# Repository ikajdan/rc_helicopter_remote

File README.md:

# RC Helicopter Remote

## Overview

This project is a custom PCB-based remote controller for an RC helicopter, built around the STM32L452RET6 microcontroller. It interfaces with two joysticks, four buttons, and two potentiometers to capture user input and transmits control data wirelessly via the NRF24L01 module to the helicopter's mainboard.

It complements the [Mainboard PCB](https://github.com/ikajdan/rc_helicopter_mainboard) and is developed in parallel with it as part of the same system.

## Features

The board features an STM32L452RET6 microcontroller, powered by a Li-Ion battery regulated to 3.3 V. It includes a 16 MHz crystal oscillator for accurate timing and clocking. Input devices such as two joysticks (X, Y, S), multiple buttons (SW1–SW4), and two analog potentiometers are connected directly to GPIO pins. Wireless communication is handled by the NRF24L01 module via SPI. Several status LEDs provide user feedback.

## PCB Design

This is a 2-layer compact PCB designed for handheld use, with easy access to controls and routing for digital and analog signals.

| Front View                            | Back View                           |
|---------------------------------------|-------------------------------------|
|  |  |

## Power Supply

The power supply uses an LTC3440 buck-boost converter to step the battery voltage down to 3.3 V. Key components include a 10 µH inductor, 22 µF output capacitor, and feedback resistors (R3 = 340 kΩ, R5 = 200 kΩ, R4 = 15 kΩ) to set the output voltage. The converter is configured for efficient operation across a wide input range and includes filtering components for stability. A power switch and 10 µF input capacitor (C10) are included for basic input protection and noise reduction.

## License

This project is licensed under the [CERN Open Hardware Licence Version 2 - Permissive (CERN-OHL-P)](https://ohwr.org/cern_ohl_p_v2.txt).
You are free to use, modify, and distribute this design, provided you retain notices and disclaimers as specified in the license terms. See the [LICENSE](LICENSE.md) file for full details.

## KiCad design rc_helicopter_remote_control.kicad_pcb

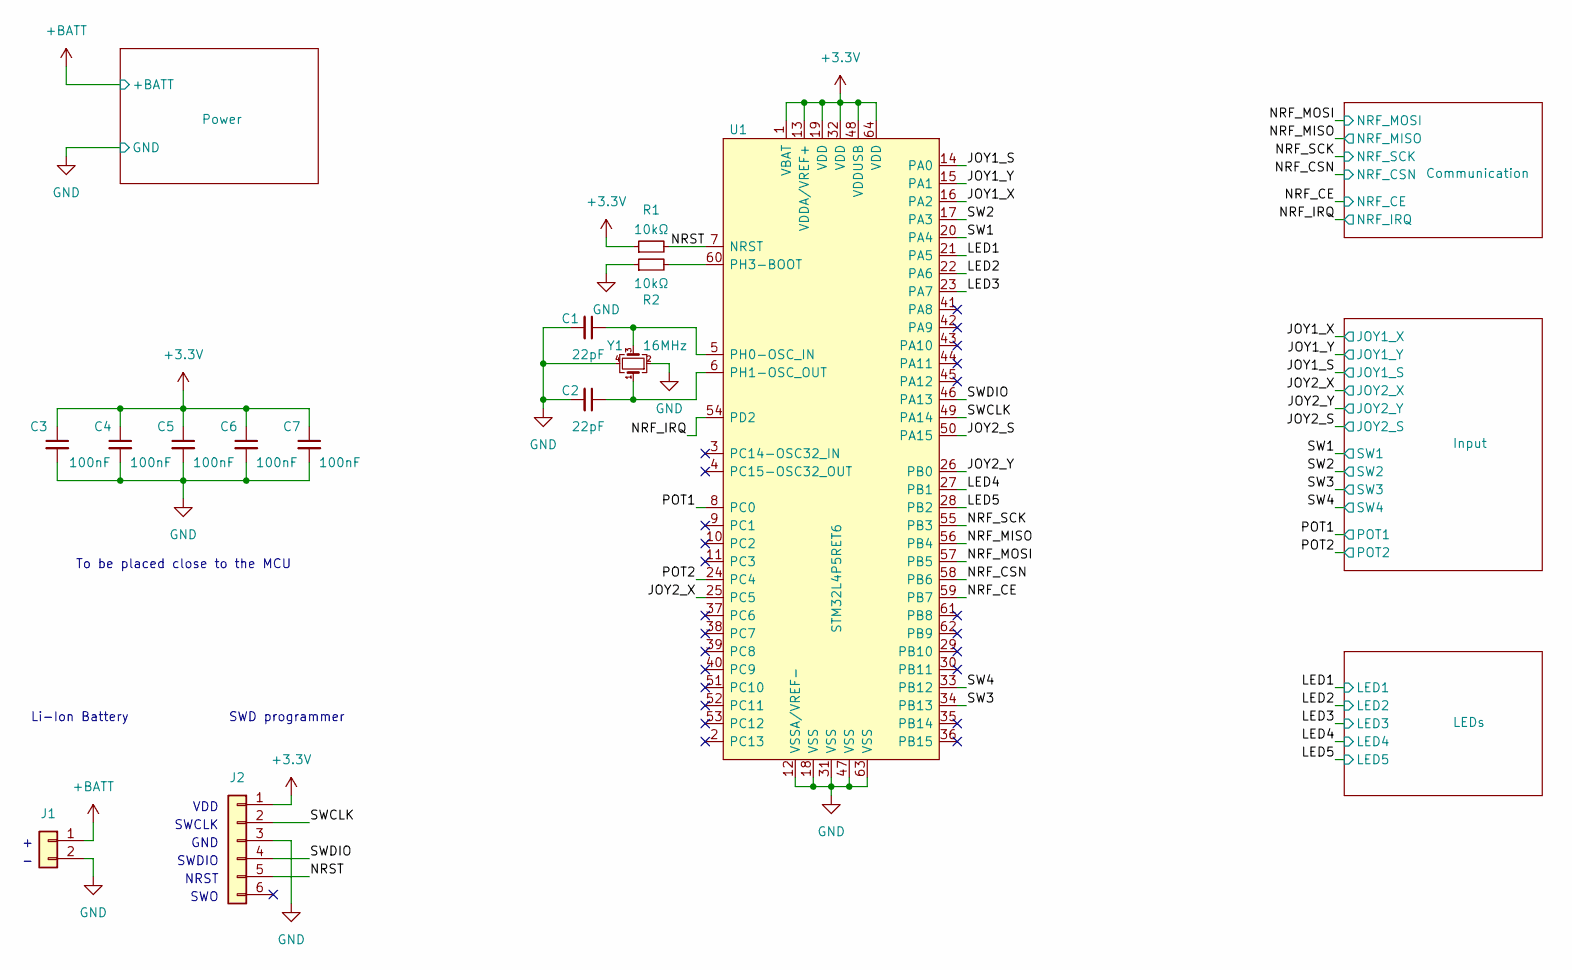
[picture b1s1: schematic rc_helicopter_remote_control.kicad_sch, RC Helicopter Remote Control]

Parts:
C1, C2: 22pF; C_0603_1608Metric
C3, C4, C5, C6, C7: 100nF; C_0603_1608Metric
J1: Battery Pack; Molex_KK-254_AE-6410-02A_1x02_P2.54mm_Vertical
J2: SWD; PinHeader_1x06_P2.54mm_Vertical_SMD_Pin1Left
R1, R2: 10kΩ; R_0603_1608Metric
U1: STM32L4P5RET6; LQFP-64_10x10mm_P0.5mm
Y1: 16MHz; Crystal_SMD_3225-4Pin_3.2x2.5mm

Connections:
+3.3V: C3.1, C4.1, C5.1, C6.1, C7.1, J2.1, R1.1, U1.1 (VBAT), U1.13 (VDDA/VREF+), U1.19 (VDD), U1.32 (VDD), U1.48 (VDDUSB), U1.64 (VDD); also elsewhere on the board
+BATT: J1.1; also elsewhere on the board
/JOY1_S: U1.14 (PA0); also elsewhere on the board
/JOY1_X: U1.16 (PA2); also elsewhere on the board
/JOY1_Y: U1.15 (PA1); also elsewhere on the board
/JOY2_S: U1.50 (PA15); also elsewhere on the board
/JOY2_X: U1.25 (PC5); also elsewhere on the board
/JOY2_Y: U1.26 (PB0); also elsewhere on the board
/LED1: U1.21 (PA5); also elsewhere on the board
/LED2: U1.22 (PA6); also elsewhere on the board
/LED3: U1.23 (PA7); also elsewhere on the board
/LED4: U1.27 (PB1); also elsewhere on the board
/LED5: U1.28 (PB2); also elsewhere on the board
/NRF_CE: U1.59 (PB7); also elsewhere on the board
/NRF_CSN: U1.58 (PB6); also elsewhere on the board
/NRF_IRQ: U1.54 (PD2); also elsewhere on the board
/NRF_MISO: U1.56 (PB4); also elsewhere on the board
/NRF_MOSI: U1.57 (PB5); also elsewhere on the board
/NRF_SCK: U1.55 (PB3); also elsewhere on the board
/NRST: J2.5, R1.2, U1.7 (NRST)
/POT1: U1.8 (PC0); also elsewhere on the board
/POT2: U1.24 (PC4); also elsewhere on the board
/SW1: U1.20 (PA4); also elsewhere on the board
/SW2: U1.17 (PA3); also elsewhere on the board
/SW3: U1.34 (PB13); also elsewhere on the board
/SW4: U1.33 (PB12); also elsewhere on the board
/SWCLK: J2.2, U1.49 (PA14)
/SWDIO: J2.4, U1.46 (PA13)
GND: C1.2, C2.2, C3.2, C4.2, C5.2, C6.2, C7.2, J1.2, J2.3, R2.1, U1.12 (VSSA/VREF-), U1.18 (VSS), U1.31 (VSS), U1.47 (VSS), U1.63 (VSS), Y1.2, Y1.4; also elsewhere on the board
unnamed: C1.1, U1.5 (PH0-OSC_IN), Y1.3
unnamed: C2.1, U1.6 (PH1-OSC_OUT), Y1.1
unnamed: R2.2, U1.60 (PH3-BOOT)

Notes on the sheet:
Li-Ion Battery
SWDIO
To be placed close to the MCU
NRST
VDD
SWD programmer
GND
SWCLK
SWO

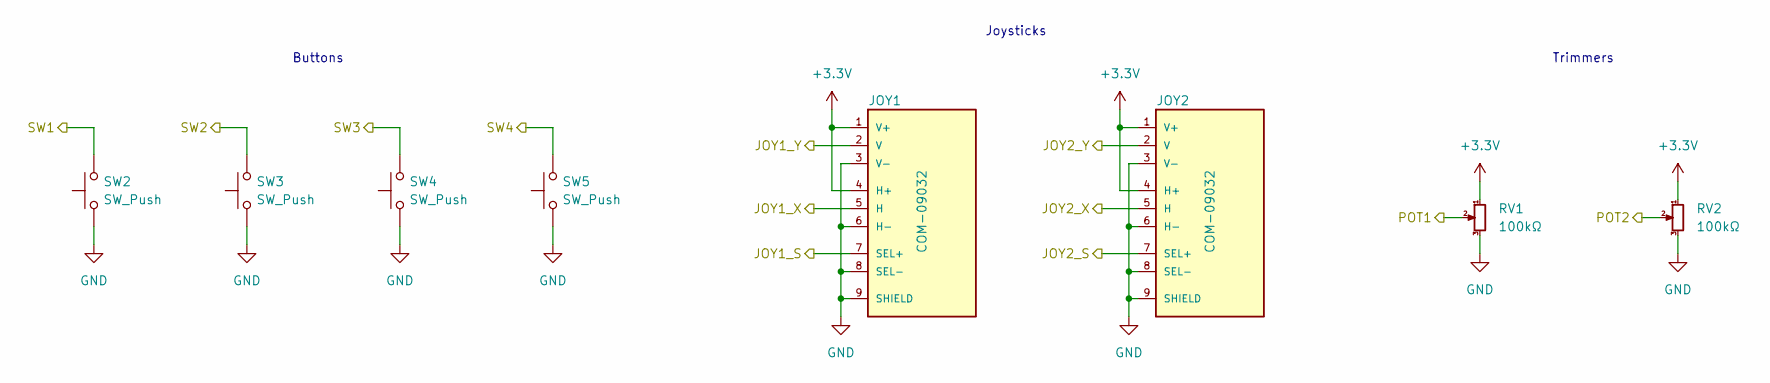
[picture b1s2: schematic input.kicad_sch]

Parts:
JOY1, JOY2: COM-09032; XDCR_COM-09032; PARTREV N/A
RV1, RV2: 100kΩ; Potentiometer_ACP_CA14V-15_Vertical
SW2, SW3, SW4, SW5: SW_Push; SW_PUSH_6mm_H13mm

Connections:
+3.3V: JOY1.1 (V+), JOY1.4 (H+), JOY2.1 (V+), JOY2.4 (H+), RV1.1, RV2.1; also elsewhere on the board
/JOY1_S: JOY1.7 (SEL+); also elsewhere on the board
/JOY1_X: JOY1.5 (H); also elsewhere on the board
/JOY1_Y: JOY1.2 (V); also elsewhere on the board
/JOY2_S: JOY2.7 (SEL+); also elsewhere on the board
/JOY2_X: JOY2.5 (H); also elsewhere on the board
/JOY2_Y: JOY2.2 (V); also elsewhere on the board
/POT1: RV1.2; also elsewhere on the board
/POT2: RV2.2; also elsewhere on the board
/SW1: SW2.1; also elsewhere on the board
/SW2: SW3.1; also elsewhere on the board
/SW3: SW4.1; also elsewhere on the board
/SW4: SW5.1; also elsewhere on the board
GND: JOY1.3 (V-), JOY1.6 (H-), JOY1.8 (SEL-), JOY1.9 (SHIELD), JOY2.3 (V-), JOY2.6 (H-), JOY2.8 (SEL-), JOY2.9 (SHIELD), RV1.3, RV2.3, SW2.2, SW3.2, SW4.2, SW5.2; also elsewhere on the board

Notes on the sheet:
Trimmers
Joysticks
Buttons

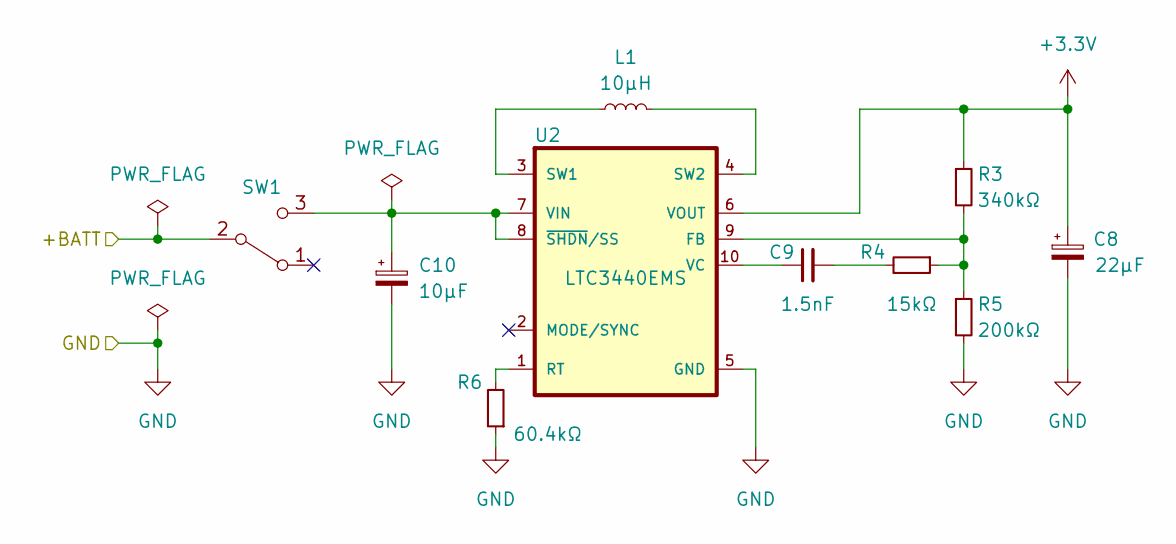
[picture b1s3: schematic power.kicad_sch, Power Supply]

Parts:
C8: 22μF; CP_Elec_6.3x5.4
C9: 1.5nF; C_0603_1608Metric
C10: 10μF; CP_Elec_6.3x5.4
L1: 10μH; L_Bourns-SRN4018
R3: 340kΩ; R_0603_1608Metric
R4: 15kΩ; R_0603_1608Metric
R5: 200kΩ; R_0603_1608Metric
R6: 60.4kΩ; R_0603_1608Metric
SW1: SW_SPST; SW_Slide_1P2T_CK_OS102011MS2Q
U2: LTC3440EMS; MSOP-10_3x3mm_P0.5mm; MPN LTC3440EMS#PBF

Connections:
+3.3V: C8.1, R3.1, U2.6 (VOUT); also elsewhere on the board
+BATT: SW1.2 (B); also elsewhere on the board
GND: C8.2, C10.2, R5.2, R6.1, U2.5 (GND); also elsewhere on the board
unnamed: C9.1, U2.10 (VC)
unnamed: C9.2, R4.2
unnamed: C10.1, SW1.3 (C), U2.7 (VIN), U2.8 (~SHDN/SS)
unnamed: L1.1, U2.3 (SW1)
unnamed: L1.2, U2.4 (SW2)
unnamed: R3.2, R4.1, R5.1, U2.9 (FB)
unnamed: R6.2, U2.1 (RT)

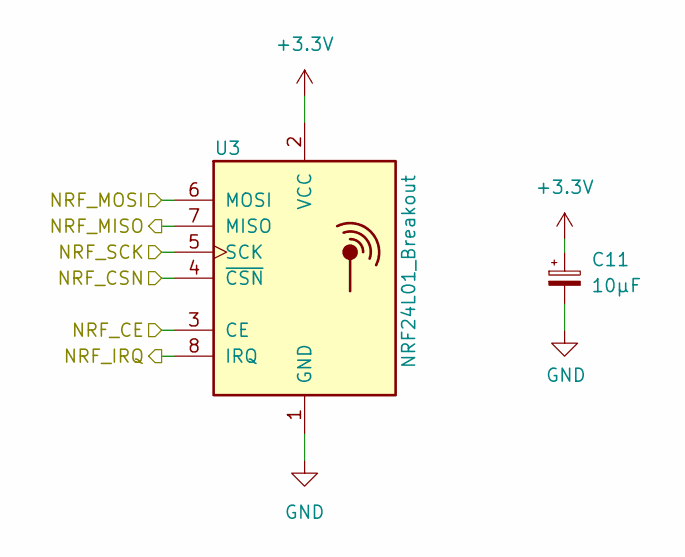
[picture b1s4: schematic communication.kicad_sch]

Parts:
C11: 10μF; CP_EIA-3216-10_Kemet-I
U3: NRF24L01_Breakout; nRF24L01_Breakout

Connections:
+3.3V: C11.1, U3.2 (VCC); also elsewhere on the board
/NRF_CE: U3.3 (CE); also elsewhere on the board
/NRF_CSN: U3.4 (~CSN); also elsewhere on the board
/NRF_IRQ: U3.8 (IRQ); also elsewhere on the board
/NRF_MISO: U3.7 (MISO); also elsewhere on the board
/NRF_MOSI: U3.6 (MOSI); also elsewhere on the board
/NRF_SCK: U3.5 (SCK); also elsewhere on the board
GND: C11.2, U3.1 (GND); also elsewhere on the board

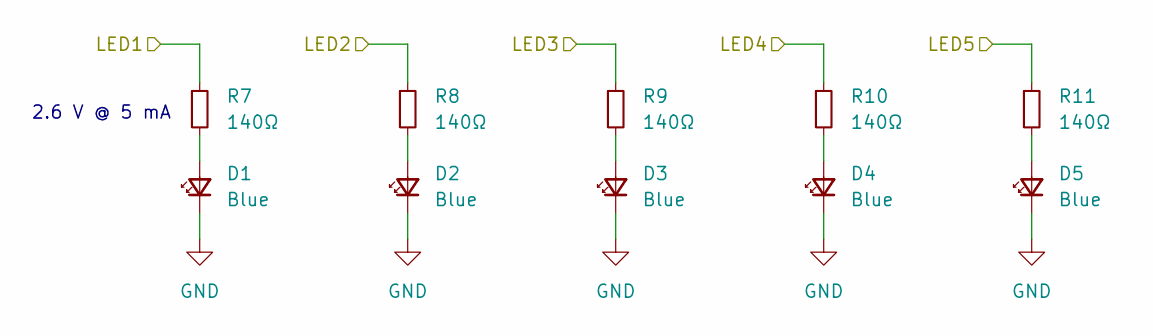
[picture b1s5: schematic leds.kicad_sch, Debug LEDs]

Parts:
D1, D2, D3, D4, D5: Blue; LED_0603_1608Metric
R7, R8, R9, R10, R11: 140Ω; R_0603_1608Metric

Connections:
/LED1: R7.1; also elsewhere on the board
/LED2: R8.1; also elsewhere on the board
/LED3: R9.1; also elsewhere on the board
/LED4: R10.1; also elsewhere on the board
/LED5: R11.1; also elsewhere on the board
GND: D1.1 (K), D2.1 (K), D3.1 (K), D4.1 (K), D5.1 (K); also elsewhere on the board
unnamed: D1.2 (A), R7.2
unnamed: D2.2 (A), R8.2
unnamed: D3.2 (A), R9.2
unnamed: D4.2 (A), R10.2
unnamed: D5.2 (A), R11.2

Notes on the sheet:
2.6 V @ 5 mA

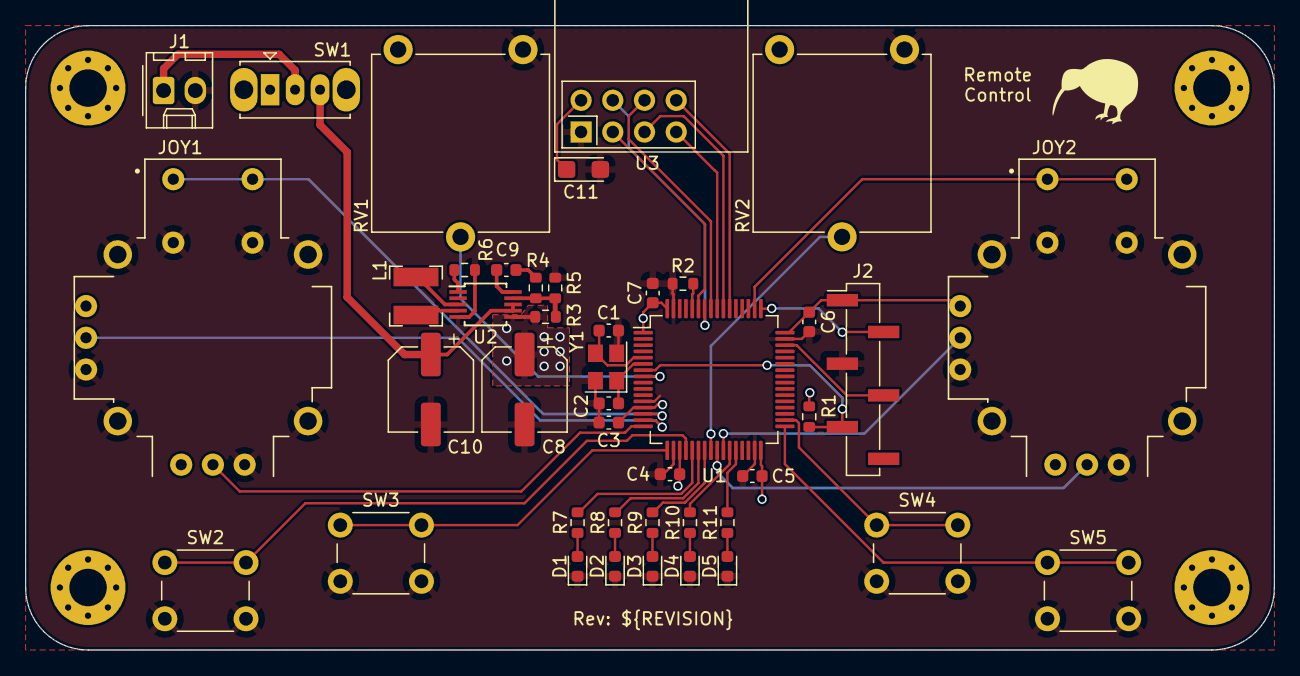
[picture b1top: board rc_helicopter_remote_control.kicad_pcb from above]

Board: 2 copper layers, 100.0 x 50.0 mm, 43 parts (0 on the bottom side), 44 nets.

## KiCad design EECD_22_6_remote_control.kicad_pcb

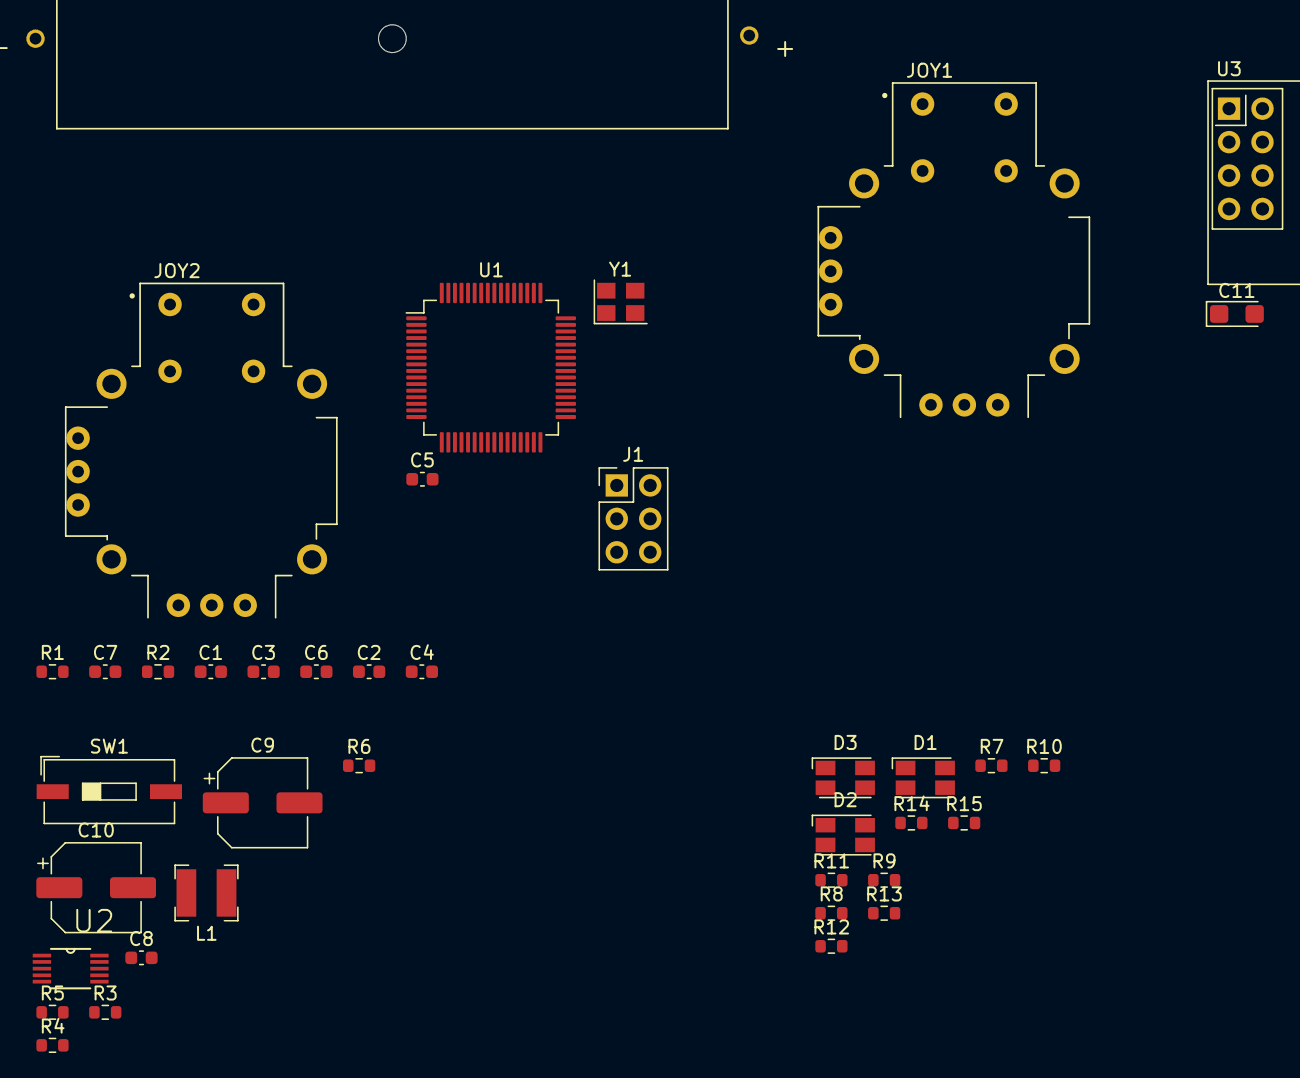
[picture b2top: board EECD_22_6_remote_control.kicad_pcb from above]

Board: 2 copper layers, 39 parts (0 on the bottom side), 47 nets, no tracks yet.

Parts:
BT1: Li-Ion; BAT_BCAAAW
C1, C2: 22pF; C_0603_1608Metric
C3, C4, C5, C6, C7: 100nF; C_0603_1608Metric
C8: 1.5nF; C_0603_1608Metric
C9: 22μF; CP_Elec_6.3x5.4
C10: 10μF; CP_Elec_6.3x5.4
C11: 10μF; CP_EIA-3216-10_Kemet-I
D1, D2, D3: LED_RGBK; LED_Avago_PLCC4_3.2x2.8mm_CW
J1: SWD; PinHeader_2x03_P2.54mm_Vertical
JOY1, JOY2: COM-09032; XDCR_COM-09032
L1: 10μH; L_Bourns-SRN4018
R1, R2: 10kΩ; R_0603_1608Metric
R3: 340kΩ; R_0603_1608Metric
R4: 15kΩ; R_0603_1608Metric
R5: 60.4kΩ; R_0603_1608Metric
R6: 200kΩ; R_0603_1608Metric
R7, R8, R9: 180Ω; R_0603_1608Metric
R10, R11, R12, R13, R14, R15: 100Ω; R_0603_1608Metric
SW1: SW_SPST; SW_DIP_SPSTx01_Slide_9.78x4.72mm_W8.61mm_P2.54mm
U1: STM32L4P5RET6; LQFP-64_10x10mm_P0.5mm
U2: LTC3440EMS; SOP50P490X110-10N
U3: NRF24L01_Breakout; nRF24L01_Breakout
Y1: 16MHz; Crystal_SMD_3225-4Pin_3.2x2.5mm

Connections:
+3.3V: C3.1, C4.1, C5.1, C6.1, C7.1, C9.2, C11.1, D1.4 (K), D2.4 (K), D3.4 (K), J1.1, JOY1.H1 (H+), JOY1.V1 (V+), JOY2.H1 (H+), JOY2.V1 (V+), R1.1, R3.1, U1.1 (VBAT), U1.13 (VDDA/VREF+), U1.19 (VDD), U1.32 (VDD), U1.48 (VDDUSB), U1.64 (VDD), U2.6 (VOUT), U3.2 (VCC)
+BATT: BT1.1 (+), SW1.1 (A)
/JOY1_S: JOY1.B1A (SEL+), U1.16 (PA2)
/JOY1_X: JOY1.H2 (H), U1.15 (PA1)
/JOY1_Y: JOY1.V2 (V), U1.14 (PA0)
/JOY2_S: JOY2.B1A (SEL+), U1.44 (PA11)
/JOY2_X: JOY2.H2 (H), U1.43 (PA10)
/JOY2_Y: JOY2.V2 (V), U1.42 (PA9)
/LED1_B: R13.2, U1.62 (PB9)
/LED1_G: R10.2, U1.61 (PB8)
/LED1_R: R7.2, U1.59 (PB7)
/LED2_B: R14.2, U1.33 (PB12)
/LED2_G: R11.2, U1.30 (PB11)
/LED2_R: R8.2, U1.29 (PB10)
/LED3_B: R15.2, U1.36 (PB15)
/LED3_G: R12.2, U1.35 (PB14)
/LED3_R: R9.2, U1.34 (PB13)
/NRF_CE: U1.26 (PB0), U3.3 (CE)
/NRF_CSN: U1.20 (PA4), U3.4 (~CSN)
/NRF_IRQ: U1.41 (PA8), U3.8 (IRQ)
/NRF_MISO: U1.22 (PA6), U3.7 (MISO)
/NRF_MOSI: U1.23 (PA7), U3.6 (MOSI)
/NRF_SCK: U1.21 (PA5), U3.5 (SCK)
/NRST: J1.5, R1.2, U1.7 (NRST)
/Power/FB: R3.2, R4.1, R6.1, U2.9 (FB)
/SWCLK: J1.2, U1.49 (PA14)
/SWDIO: J1.4, U1.46 (PA13)
/SWO: J1.6, U1.55 (PB3)
GND: BT1.2 (-), C1.2, C2.2, C3.2, C4.2, C5.2, C6.2, C7.2, C9.1, C10.2, C11.2, J1.3, JOY1.B2A (SEL-), JOY1.H3 (H-), JOY1.S1 (SHIELD), JOY1.S2 (SHIELD), JOY1.S3 (SHIELD), JOY1.S4 (SHIELD), JOY1.V3 (V-), JOY2.B2A (SEL-), JOY2.H3 (H-), JOY2.S1 (SHIELD), JOY2.S2 (SHIELD), JOY2.S3 (SHIELD), JOY2.S4 (SHIELD), JOY2.V3 (V-), R2.1, R5.2, R6.2, U1.12 (VSSA/VREF-), U1.18 (VSS), U1.31 (VSS), U1.47 (VSS), U1.63 (VSS), U2.5 (GND), U3.1 (GND), Y1.2, Y1.4
unnamed: C1.1, U1.5 (PH0-OSC_IN), Y1.3
unnamed: C2.1, U1.6 (PH1-OSC_OUT), Y1.1
unnamed: C8.1, U2.10 (VC)
unnamed: C8.2, R4.2
unnamed: C10.1, SW1.2 (B), U2.7 (VIN), U2.8 (~SHDN/SS)
unnamed: D1.1 (RA), R7.1
unnamed: D1.2 (GA), R10.1
unnamed: D1.3 (BA), R13.1
unnamed: D2.1 (RA), R8.1
unnamed: D2.2 (GA), R11.1
unnamed: D2.3 (BA), R14.1
unnamed: D3.1 (RA), R9.1
unnamed: D3.2 (GA), R12.1
unnamed: D3.3 (BA), R15.1
unnamed: L1.1, U2.3 (SW1)
unnamed: L1.2, U2.4 (SW2)
unnamed: R2.2, U1.60 (PH3-BOOT)
unnamed: R5.1, U2.1 (RT)

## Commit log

2022-11-22 you can understand at least smth now
2022-12-20 normal power supply + footprints
2022-12-28 Add gitignore
2022-12-28 Move project files to the top directory
2022-12-28 Apply custom drawing sheet and project settings
2022-12-28 Configure local libraries
2022-12-28 Schematic refactor
    - Divide the schematic into hierarchical sheets
    - Fix ERCs
    - Remove unused footprints
    - Add SWD connector
    - Add bypass capacitors
2022-12-28 Use proper footprints for custom symbols
2022-12-28 Rename the project
2022-12-29 Improve DCDC converter diagram
2022-12-29 Replace RGB leds with single color ones
2022-12-29 Add buttons and trimmers
2022-12-29 Arrange footprints
2022-12-30 Use more appropriate MCU pins for peripherals
2023-01-09 Route PCB tracks
2023-01-10 Improve the routing
2023-01-17 Release v1.0.0
2025-06-22 Refactor the project
